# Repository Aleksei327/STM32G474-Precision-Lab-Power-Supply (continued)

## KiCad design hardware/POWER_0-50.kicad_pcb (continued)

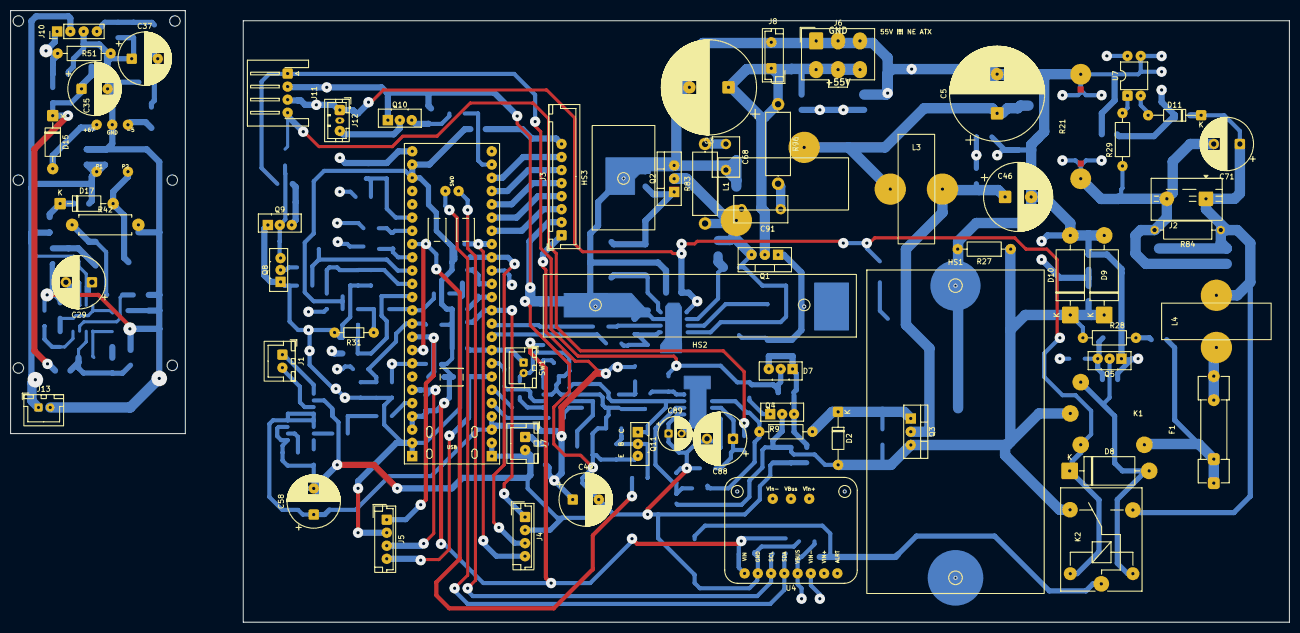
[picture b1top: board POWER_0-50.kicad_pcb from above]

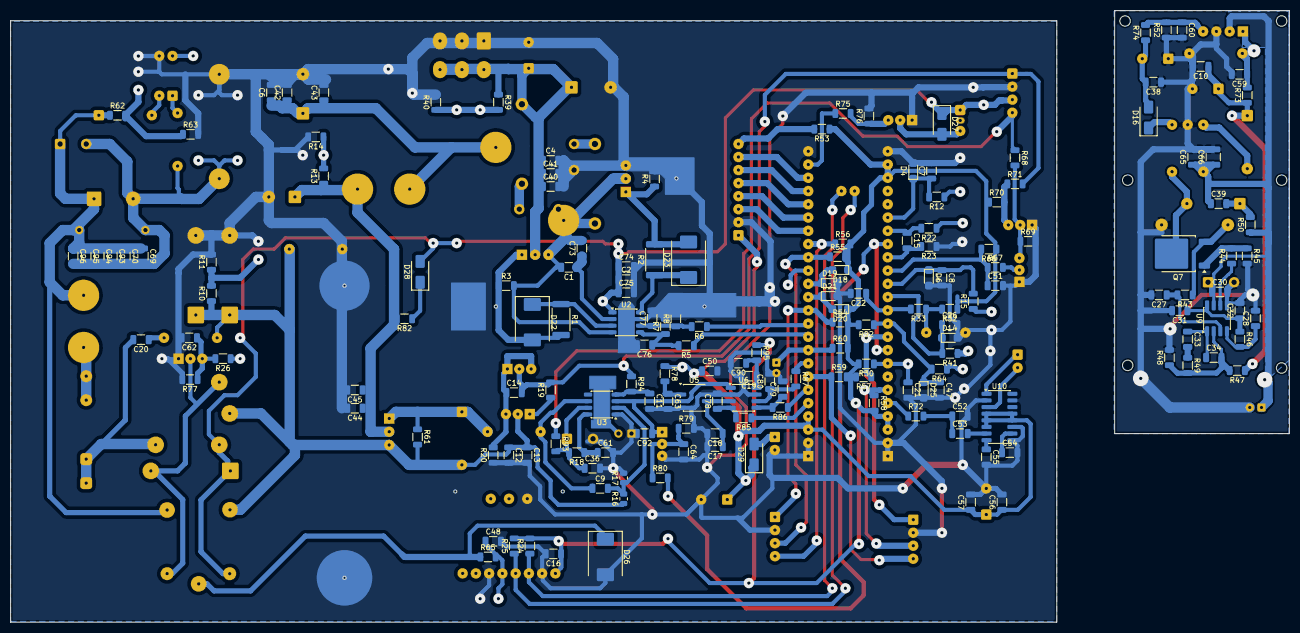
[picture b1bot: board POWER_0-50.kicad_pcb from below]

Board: 4 copper layers, 200.5 x 115.3 mm, 235 parts (168 on the bottom side), 115 nets.

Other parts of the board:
HS1: Heatsink_Amp_62x40x34
HS2: Heatsink_Profile_60mm
HS3: Heatsink_Profile_20mm

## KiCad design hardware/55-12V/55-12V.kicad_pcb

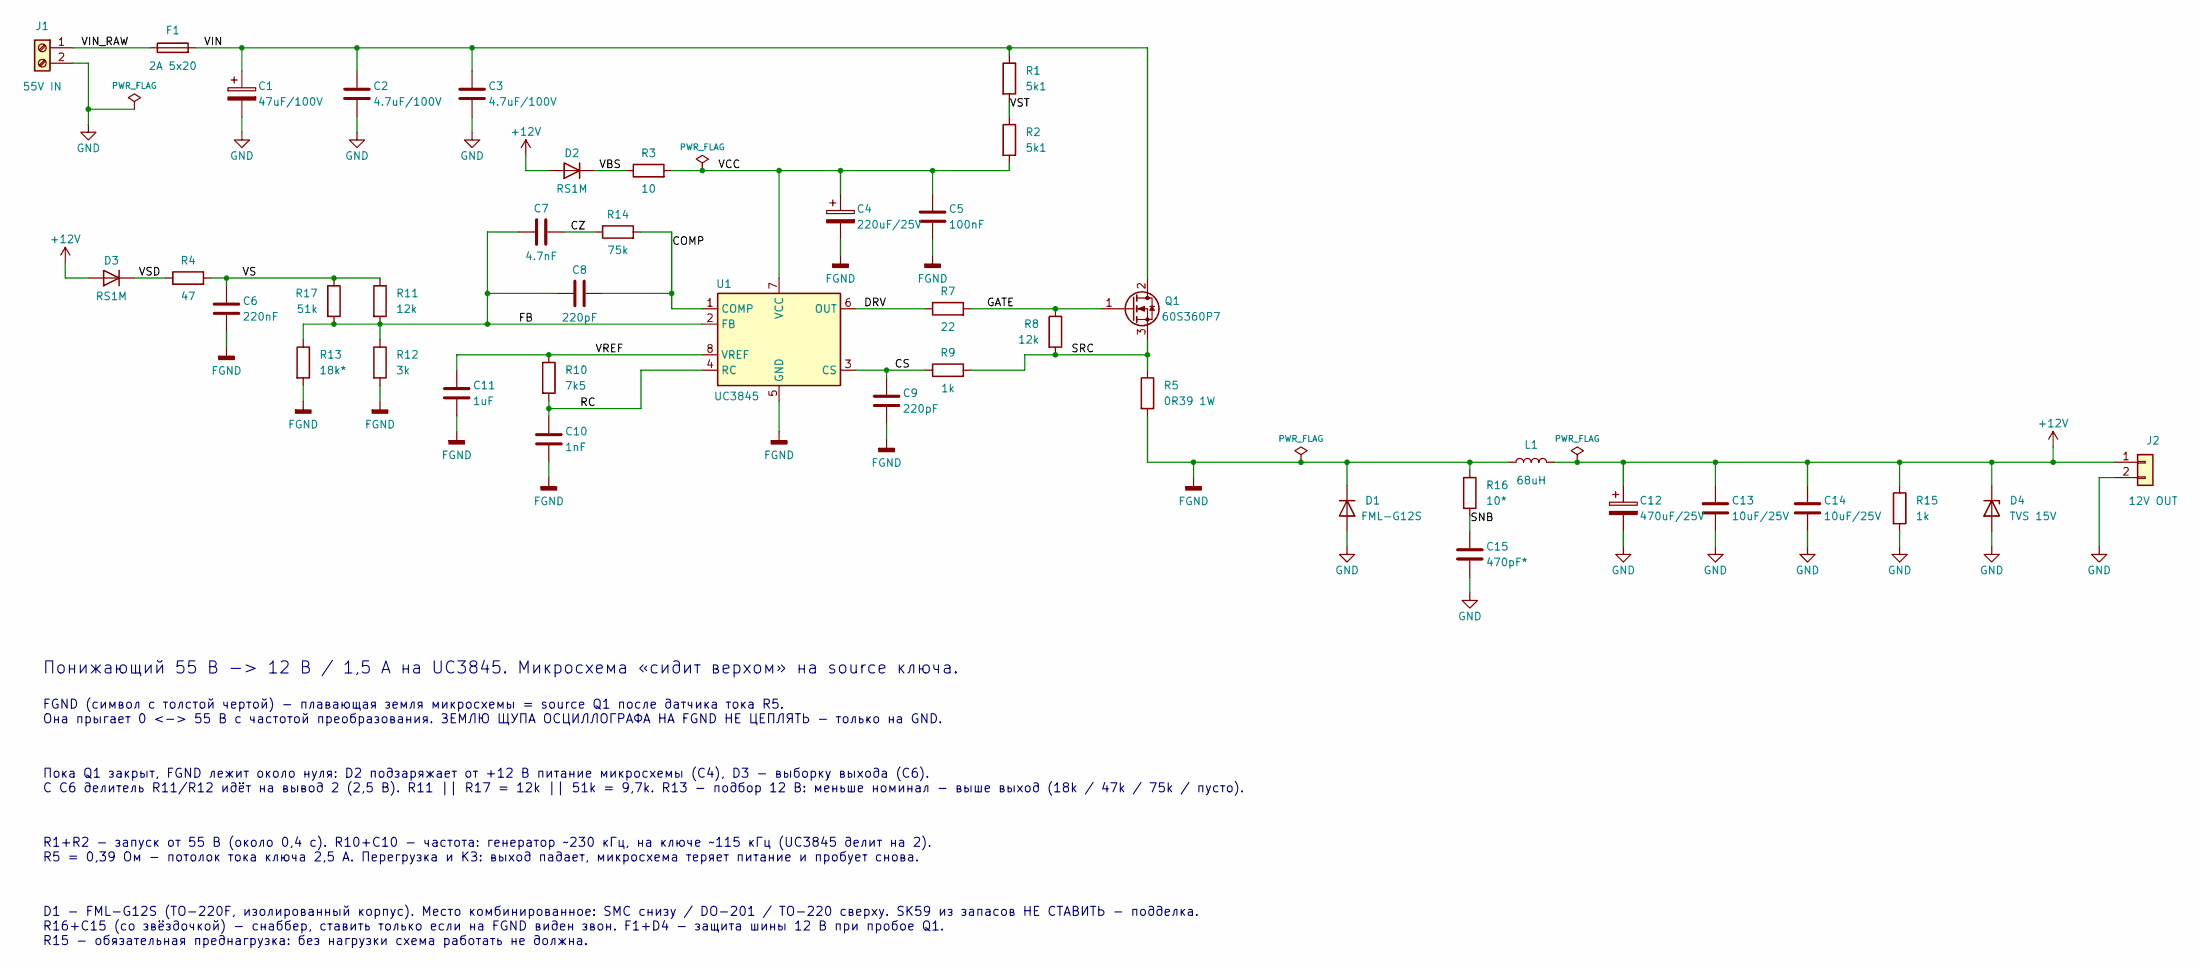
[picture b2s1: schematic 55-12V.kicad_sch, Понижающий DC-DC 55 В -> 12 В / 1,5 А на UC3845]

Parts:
C1: 47uF/100V; CP_Radial_D10.0mm_P5.00mm_D0.6
C2, C3: 4.7uF/100V; C_1206_3216Metric
C4: 220uF/25V; CP_Radial_D8.0mm_P5.00mm_D0.6
C5: 100nF; C_Combo_1206_Disc_P3.80mm
C6: 220nF; C_Combo_1206_Disc_P3.80mm
C7: 4.7nF; C_Combo_1206_Disc_P3.80mm
C8, C9: 220pF; C_Combo_1206_Disc_P3.80mm
C10: 1nF; C_Combo_1206_Disc_P5.08mm
C11: 1uF; C_1206_3216Metric
C12: 470uF/25V; CP_Radial_D10.0mm_P5.00mm_D0.6
C13, C14: 10uF/25V; C_1206_3216Metric
C15: 470pF*; C_Combo_1206_Disc_P3.80mm
D1: FML-G12S; D_Combo_SMC_Axial_P15.24mm_TO-220
D2, D3: RS1M; D_SMA
D4: TVS 15V; D_Combo_SMC_Axial_P15.24mm_TO-220
F1: 2A 5x20; Fuseholder_5x20mm_P20.00mm_Body23.5x9.5mm_D0.6
J1: 55V IN; TerminalBlock_1x02_P5.00mm_D0.6
J2: 12V OUT; Conn_WirePads_1x02_P5.08mm_Pad3.4mm_D0.6
L1: 68uH; L_SMD_15x15mm
Q1: 60S360P7; TO-252-2
R1, R2: 5k1; R_1206_3216Metric
R3: 10; R_1206_3216Metric
R4: 47; R_1206_3216Metric
R5: 0R39 1W; R_Axial_P15.24mm_Pad3.2mm_D0.6
R7: 22; R_1206_3216Metric
R8, R11: 12k; R_1206_3216Metric
R9, R15: 1k; R_1206_3216Metric
R10: 7k5; R_1206_3216Metric
R12: 3k; R_1206_3216Metric
R13: 18k*; R_1206_3216Metric
R14: 75k; R_1206_3216Metric
R16: 10*; R_1206_3216Metric
R17: 51k; R_1206_3216Metric
U1: UC3845; SOIC-8_3.9x4.9mm_P1.27mm_Pad0.8mm

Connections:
+12V: C12.1, C13.1, C14.1, D2.2 (A), D3.2 (A), D4.1 (K), J2.1, L1.2, R15.1
/COMP: C8.2, R14.2, U1.1 (COMP)
/CS: C9.1, R9.1, U1.3 (CS)
/CZ: C7.2, R14.1
/DRV: R7.1, U1.6 (OUT)
/FB: C7.1, C8.1, R11.2, R12.1, R13.1, R17.2, U1.2 (FB)
/GATE: Q1.1 (G), R7.2, R8.1
/RC: C10.1, R10.2, U1.4 (RC)
/SNB: C15.1, R16.2
/SRC: Q1.3 (S), R5.1, R8.2, R9.2
/VBS: D2.1 (K), R3.1
/VCC: C4.1, C5.1, R2.2, R3.2, U1.7 (VCC)
/VIN: C1.1, C2.1, C3.1, F1.2, Q1.2 (D), R1.1
/VIN_RAW: F1.1, J1.1
/VREF: C11.1, R10.1, U1.8 (VREF)
/VS: C6.1, R4.2, R11.1, R17.1
/VSD: D3.1 (K), R4.1
/VST: R1.2, R2.1
FGND: C4.2, C5.2, C6.2, C9.2, C10.2, C11.2, D1.1 (K), L1.1, R5.2, R12.2, R13.2, R16.1, U1.5 (GND)
GND: C1.2, C2.2, C3.2, C12.2, C13.2, C14.2, C15.2, D1.2 (A), D4.2 (A), J1.2, J2.2, R15.2

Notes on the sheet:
Понижающий 55 В -> 12 В / 1,5 А на UC3845. Микросхема «сидит верхом» на source ключа.
FGND (символ с толстой чертой) - плавающая земля микросхемы = source Q1 после датчика тока R5. Она прыгает 0 <-> 55 В с частотой преобразования. ЗЕМЛЮ ЩУПА ОСЦИЛЛОГРАФА НА FGND НЕ ЦЕПЛЯТЬ - только на GND.
Пока Q1 закрыт, FGND лежит около нуля: D2 подзаряжает от +12 В питание микросхемы (C4), D3 - выборку выхода (C6). С C6 делитель R11/R12 идёт на вывод 2 (2,5 В). R11 || R17 = 12k || 51k = 9,7k. R13 - подбор 12 В: меньше номинал - выше выход (18k / 47k / 75k / пусто).
R1+R2 - запуск от 55 В (около 0,4 с). R10+C10 - частота: генератор ~230 кГц, на ключе ~115 кГц (UC3845 делит на 2). R5 = 0,39 Ом - потолок тока ключа 2,5 А. Перегрузка и КЗ: выход падает, микросхема теряет питание и пробует снова.
D1 - FML-G12S (TO-220F, изолированный корпус). Место комбинированное: SMC снизу / DO-201 / TO-220 сверху. SK59 из запасов НЕ СТАВИТЬ - подделка. R16+C15 (со звёздочкой) - снаббер, ставить только если на FGND виден звон. F1+D4 - защита шины 12 В при пробое Q1. R15 - обязательная преднагрузка: без на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

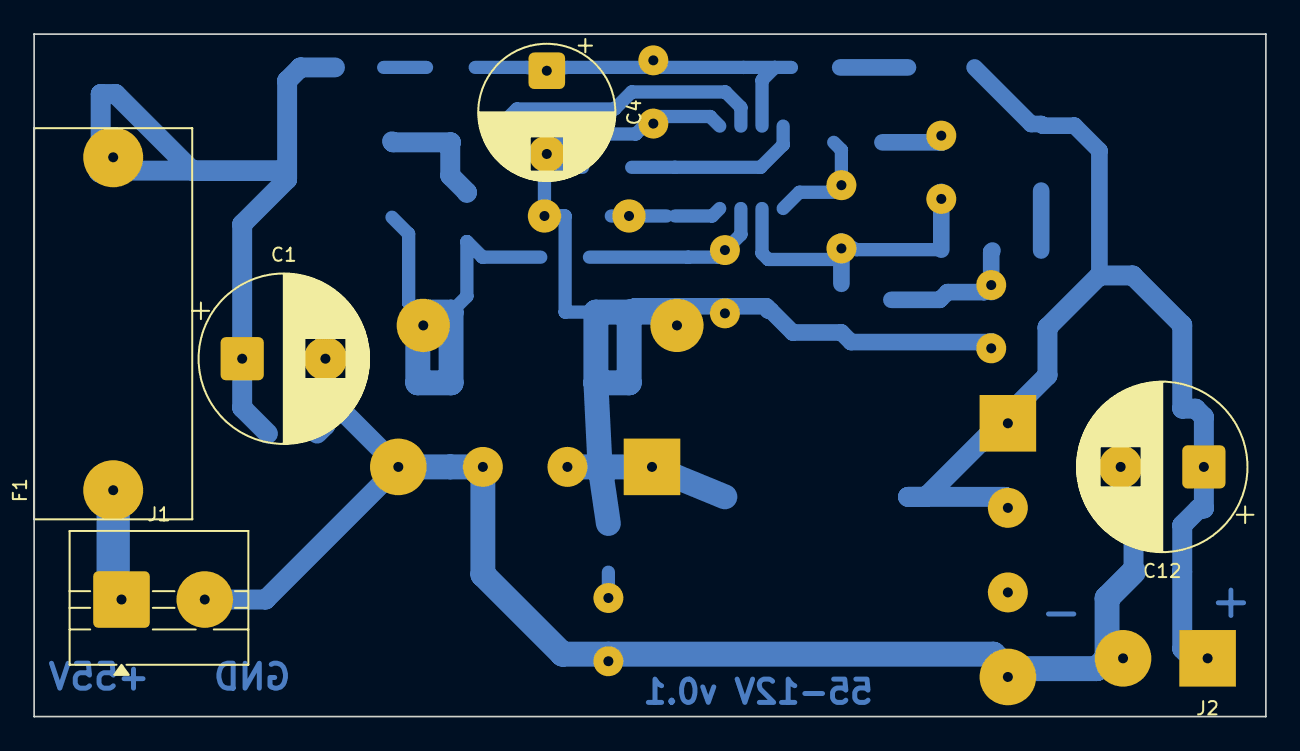
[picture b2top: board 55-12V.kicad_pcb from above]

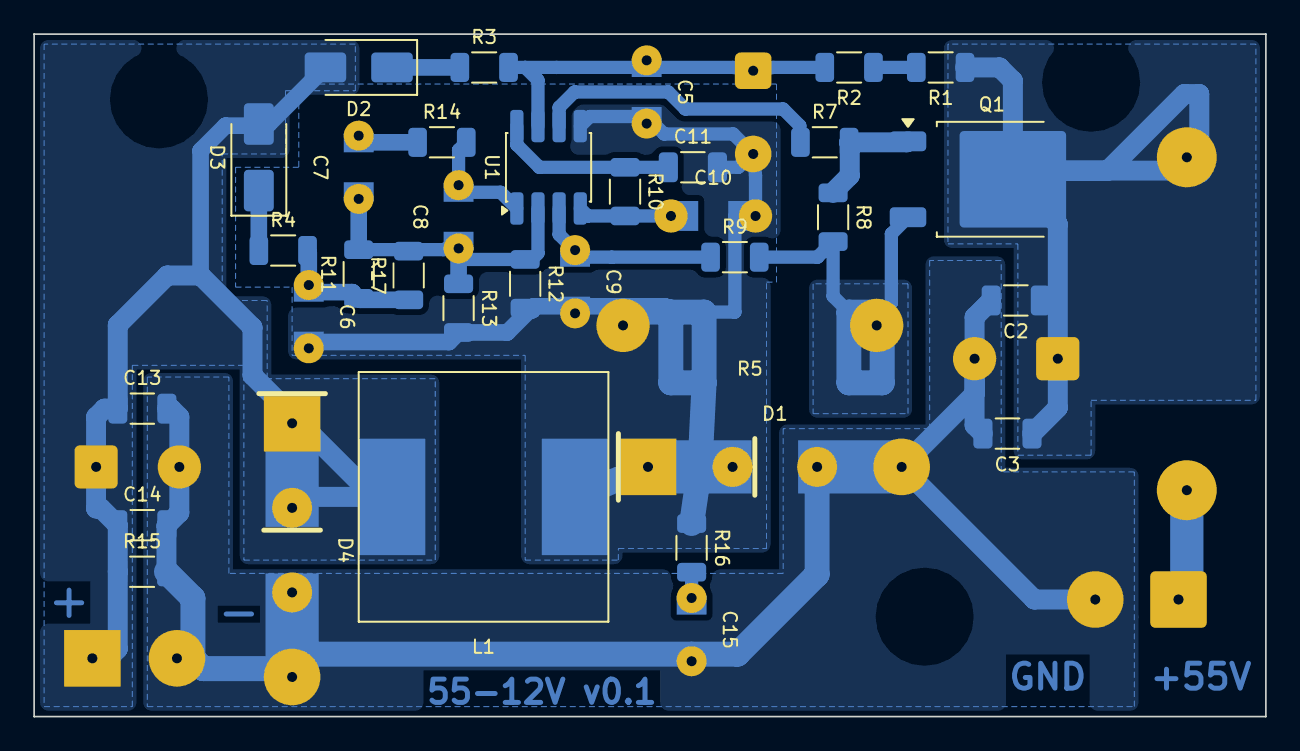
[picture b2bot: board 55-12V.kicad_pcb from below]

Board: 2 copper layers, 74.0 x 41.0 mm, 41 parts (35 on the bottom side), 20 nets.

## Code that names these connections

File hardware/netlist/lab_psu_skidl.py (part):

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    N['VOUT_SENSE'] += rs0[2], cf0[1]
    dvo_h, dvo_l = D('BAT'), D('BAT')   # ESD/кламп ADC-входа к 3V3/GND (рек. ST)
    N['3V3'] += dvo_h[1]; N['VOUT_SENSE'] += dvo_h[2], dvo_l[1]; N['GND'] += dvo_l[2]
    # делитель VDRAIN (PA5) для трекинга Vds: 200k/10k -> ~2.5В при 53В (было 180k, замена 2026-09-14; ОБЯЗАН совпадать с PA0); series+фильтр+клампы
    rda, rdb, rds, cd = R('200k'), R('10k'), R('4k7'), C('100nF')
    N['VDRAIN'] += rda[1]; N['VDS0'] += rda[2], rdb[1], rds[1]; N['GND'] += rdb[2], cd[2]
    N['VDRAIN_SENSE'] += rds[2], cd[1]
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    N['VOUT_REG'] += rbleed[1]; N['GND'] += rbleed[2]   # 2026-10-05: R27 15k->18k (что было): 52²/18k = 0,15 Вт в 0207; разряд 9,4 мкФ τ≈0,17 с
    # 2026-10-05: R29 rrev 6k8->10k: при перевёрнутых 50 В 0,23 Вт (6k8 давал 0,34 > 0,25 Вт 0207); ET1103 CTR>=34% @1мА -> гарантированно ловит от ~9,5 В обратного (типично от ~5 В)
    # 2026-10-05: dser = 1N4007 (был 1N4148): держит ОБРАТНОЕ = выходное напряжение (до ~52В, при TVS ~77В), LED оптопары терпит 6В -> нужен >=100В
    N['OUT_MINUS'] += rrev[1]; N['REV_LED_A'] += rrev[2], PC817[1]; N['REV_LED_K'] += PC817[2], dser[2]; N['OUT_PLUS'] += dser[1]
    N['REV_DET'] += PC817[4], rpull[1], crev[1]; N['3V3'] += rpull[2]; N['GND'] += PC817[3], crev[2]
    N['3V3'] += rpu[1]; N['NTC_DIV'] += rpu[2], ntc[1], rser_n[1]; N['GND'] += ntc[2], cntc[2]
    N['NTC'] += rser_n[2], cntc[1]
    N['SPK_N'] += jspk[1]; N['SPK_P'] += jspk[2]   # v0.2.40: порядок как на плате (полярность динамика безразлична)
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    # Висящий DIM = ШИМ может быть заперт -> нет 12В -> нет ничего. Сажаем DIM на EN12 (2,9В с делителя).
    N['EN12'] += u12['DIM']
    N['V12'] += l12[2], cout12[1], rfb12a[1]; N['FB12'] += rfb12a[2], rfb12b[1], u12['FB']; N['GND'] += rfb12b[2]
    # v0.2.15: делитель V12_SENSE УДАЛЁН целиком (PC4 отдан VTERM_SENSE ещё в v0.2.1, тест-поинт был не нужен)
    rva,rvb,rvs,cv = R('200k'),R('10k'),R('4k7'),C('2x100nF/16V')   # 2026-11-15: на PA6 допаян второй 100 нФ (сдвиг VIN не лечит, но стоит)   # 2026-09-14: было 180k/22k (÷9,2 -> 6 В на АЦП при 55 В, потолок ~30 В) -> ÷21 как все
    N['VIN_55'] += rva[1]; N['DVIN'] += rva[2], rvb[1], rvs[1]; N['GND'] += rvb[2], cv[2]; N['VIN_SENSE'] += rvs[2], cv[1]
    dvin_h, dvin_l = D('BAT'), D('BAT')   # ESD-клампы VIN_SENSE к 3V3/GND
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    N['GATE_QH'] += dgh[1]; dgh[2] += qh['G']   # K -> драйвер, A -> затвор
    N['GATE_QL'] += dgl[1]; dgl[2] += ql['G']
    N['VBUCK_OUT'] += l2[1]
    N['VDRAIN'] += l2[2], cdr1[1], cdr2[1], cdamp[1]   # сток проходного (после фильтра); ОС buck (PA5) — тут
    N['GND'] += cdr1[2], cdr2[2], cdamp[2]
with Blk('B_pass'):
    rgsd = R('100k')                                   # bleed затвор-исток проходного
    rgsd[1] += qpass['G']; N['VOUT_REG'] += rgsd[2]
with Blk('F_protect'):
    # делитель напряжения КЛЕММ -> PB1 (VTERM_SENSE): видеть внешний источник ДО замыкания реле + детект залипшего реле
    rvt_a, rvt_b, rvt_s, cvt = R('200k'), R('10k'), R('4k7'), C('100nF')   # 200k (было 180k, замена 2026-09-14), ÷21 как PA0/PA5
    dvt_h, dvt_l = D('BAT'), D('BAT')
    N['OUT_PLUS'] += rvt_a[1]; N['VT0'] += rvt_a[2], rvt_b[1], rvt_s[1]; N['GND'] += rvt_b[2], cvt[2]
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    N['V_P67'] += jr_o[1], jr_i[4]   # пин 1 = +67 (у J11 порядок обратный)
    N['V12'] += jr_o[2], jr_i[3]     # пин 2 = +12 (у J11 — 3)
    N['V_N5'] += jr_o[4], jr_i[1]    # пин 4 = -5 (пин 3 = GND между ними)
    # RAILS_BTN (v0.2.2): детект +67/−5 лесенкой на PA4 вместе с кнопкой RESET_FAULT.
    # Уровни PA4: ~0 = кнопка (панель, на GND), ~1,65В = рельсы ОК, ~3,3В = FAIL.
    # +67 И −5 живы => +12/MP9486/UC3845 живы (флайбэк питается от +12) — отдельный тест +12 не нужен.
    q_r67, q_r5 = NPN('D882'), NPN('D882')
    r_up, r_mid, rb67, rbe = R('10k'), R('10k'), R('680k'), R('100k')
    rq2a, rq2b, cflt = R('100k'), R('51k'), C('100nF')   # 2026-10-04: 47k->51k (что было при сборке): база Q2 при -5 = -2,2 В (закрыт), без -5 = +1,1 В (открыт); порог ~-0,85 В
    N['3V3'] += r_up[1], rq2a[1]
    N['RAILS_BTN'] += r_up[2], r_mid[1], cflt[1]                     # узел PA4
    N['RAILS_Q1C'] += r_mid[2], q_r67['C']
    N['RAILS_Q1B'] += q_r67['B'], rb67[2], rbe[1], q_r5['C']         # Q2 глушит Q1 при пропаже −5
    N['V_P67'] += rb67[1]
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    N['GND'] += q_r67['E'], q_r5['E'], rbe[2], cflt[2]

with Blk('F_protect'):
    # v0.2.21: PAM8403 Class-D моно (левый канал). Вход: PB11(BUZZER,PWM ~300кГц) -> RC ФНЧ -> разд.конд -> INL.
    pam = CHIP('PAM8403','Local:SOIC-16_3.9x9.9mm_P1.27mm_Pad0.8mm')
    rpwm, cpwm, cinl = R('3k'), C('10nF'), C('1uF')      # ФНЧ ~5,3кГц + разделительный (2026-10-04: 2k2->3k, что было при сборке; 300 кГц ШИМ давится на ~35 дБ)
    cinr, cvref, cvdd = C('1uF'), C('1uF'), C('100nF')
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    N['EN_LIN'] += ced[1]; N['GND'] += ced[2]

with Blk('H_ui'):
    # v0.2.23: вентилятор 12В (PB9 = FAN_DRV, был голым пином U1.47): BD139 low-side (запасы; освободился от пищалки).
    # Ib=(3,3-0,7)/470 ≈ 5,5 мА, hFE(min)~40 -> до ~200 мА кол-ра: типовой 80мм 12В (~100-150 мА) в насыщении.
    # 10к Б-Э держит ключ запертым при ресете MCU; SS14 гасит выброс мотора; до прошивки FAN- можно перемкнуть на GND.
    # v0.2.39: вентилятор AVC F7015T12UY = 12В/0,4А (серверный 70x15). База 470 Ом давала Ib=5,5мА,
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
with Blk('F_protect'):
    # v0.2.33: защита базы Q5 (драйвер реле) — ставится ПРЯМО У ТРАНЗИСТОРА.
    # 10к Б-Э: пока МК в ресете, PA15 = вход, а трасса RELAY_DRV длиной ~120 мм ловит наводки —
    # без подтяжки BD139 может приоткрыться = самопроизвольное включение реле (напряжение на клеммах!).
    # Потеря тока базы 75 мкА из 2,55 мА, насыщение не страдает (нужно 63 мА на две катушки, hFE>=26).
    # 10нФ Б-Э: гасит ёмкостную наводку с длинной дорожки (импульсный заряд даёт милливольты вместо вольт);
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# 2) ЦАП DAC8830 (U6): помеха buck портила посылку по SPI2, в ЦАП защёлкивался чужой код, выход сам уходил 12 -> 14 В.
#    RC у самого ЦАП: 100 Ом в разрыв линии, 100 пФ с ножки ЦАП на землю. Размах на клеммах 190 мВ -> 3,4 мВ.
with Blk('E_vset'):
    for _old, _new, _pin in (('DAC_V_SYNC', 'DAC_V_SYNC_F', 'CS'), ('SPI2_SCK', 'SPI2_SCK_F', 'SCLK'),
                             ('SPI2_DIN', 'SPI2_DIN_F', 'SDI')):
        dac[_pin].disconnect()
        _r, _c = R('100'), C('100pF/50V')
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#    Плюс ферритовое кольцо на жгуте дисплея (механика, в нетлисте его нет).
tft_flt = []   # v0.2.58: эти детали в самом конце снимаются с платы (фильтр живёт у экрана)
with Blk('H_ui'):
    for _old, _new, _pin in (('SPI1_SCK', 'SPI1_SCK_F', 3), ('SPI1_MOSI', 'SPI1_MOSI_F', 5),
                             ('TFT_CS', 'TFT_CS_F', 6), ('TFT_DC', 'TFT_DC_F', 7)):
        jtft[_pin].disconnect()
        _r, _c = R('100'), C('100pF/50V')
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# в нетлисте и на плате его нет: J3.3/5/6/7 снова прямо на SPI1_SCK / SPI1_MOSI / TFT_CS / TFT_DC.
# Убирается ЗДЕСЬ, в самом конце: номера остальных деталей (и R92 подтяжки клемм) не едут.
default_circuit.rmv_parts(*tft_flt, crst, ctv1, ctv2)
for _old, _pin in (('SPI1_SCK', 3), ('SPI1_MOSI', 5), ('TFT_CS', 6), ('TFT_DC', 7)):
    jtft[_pin].disconnect()
    N[_old] += jtft[_pin]

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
